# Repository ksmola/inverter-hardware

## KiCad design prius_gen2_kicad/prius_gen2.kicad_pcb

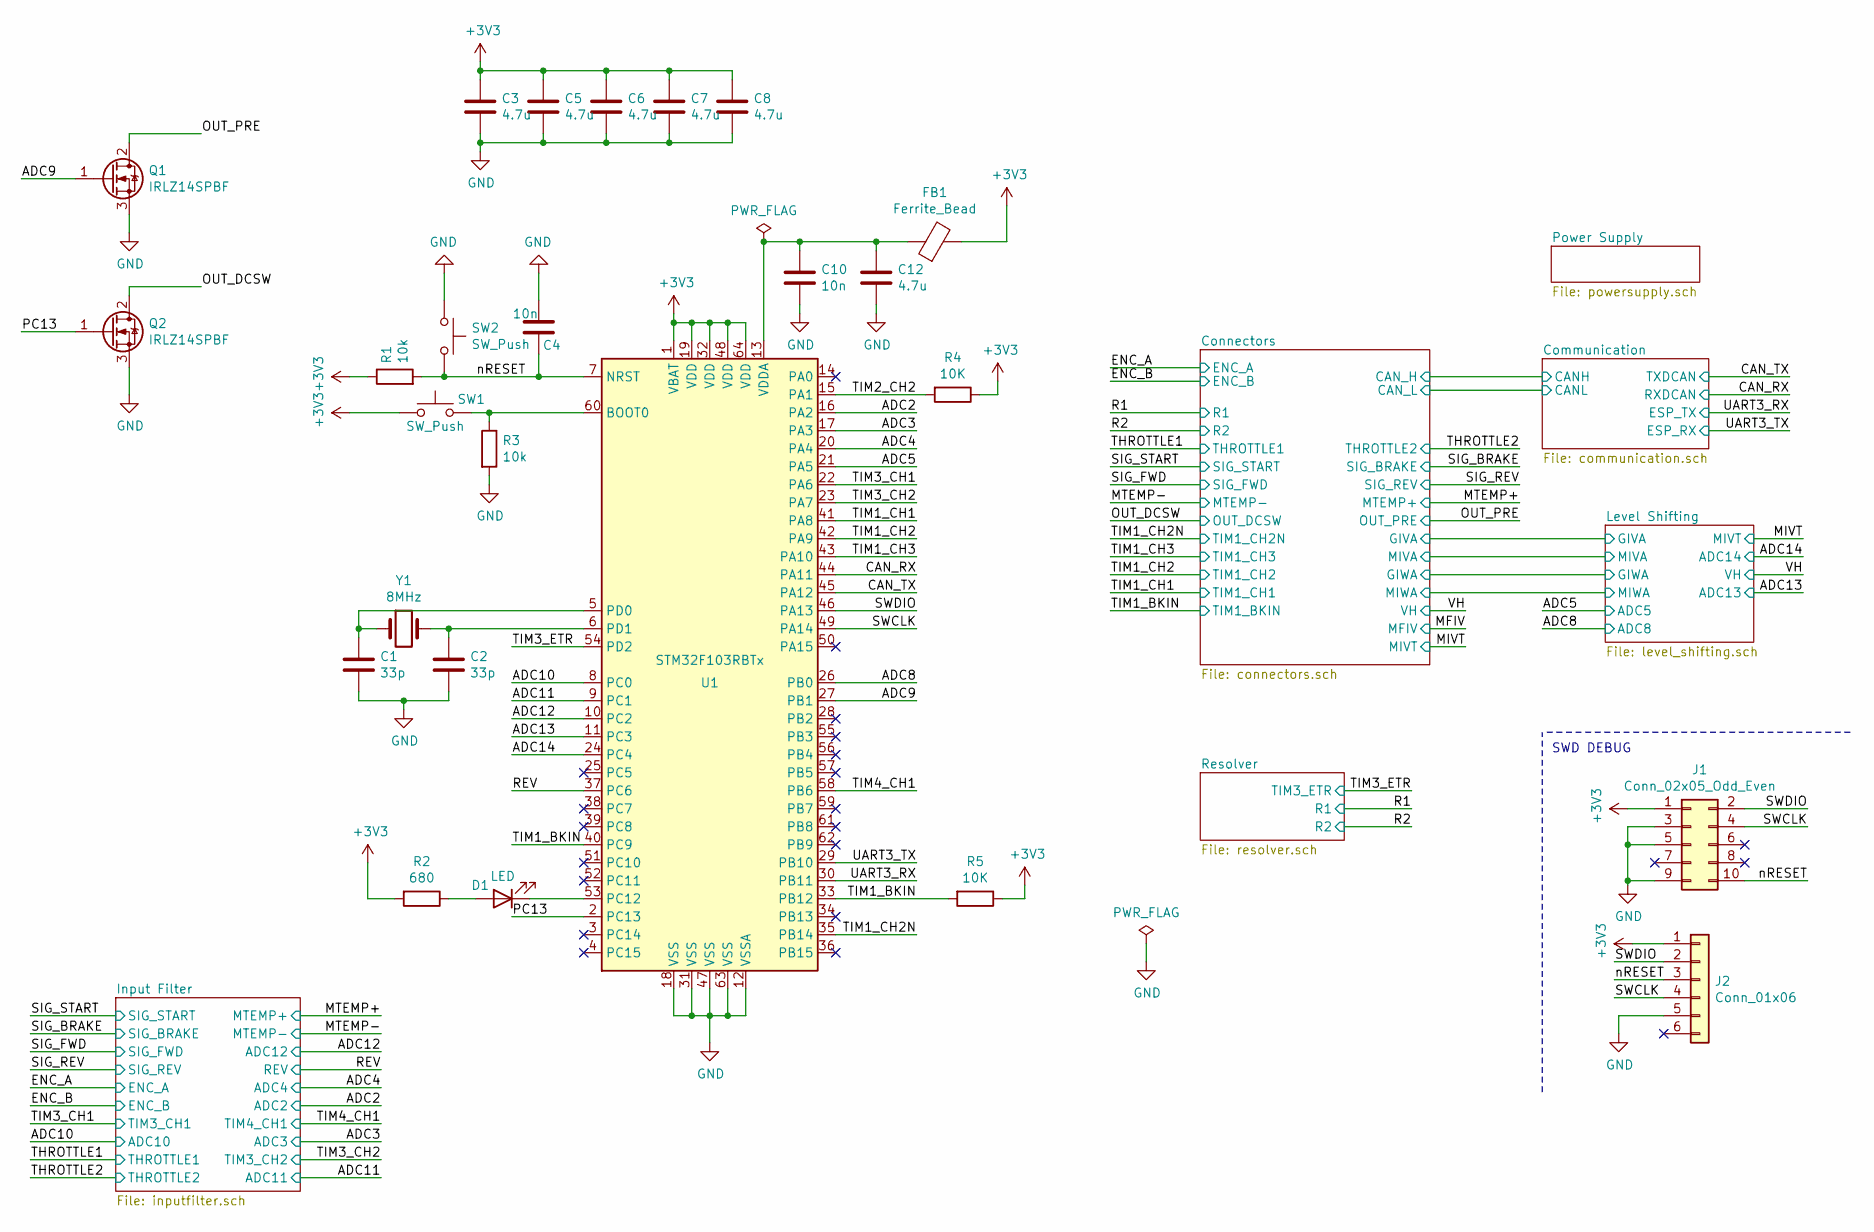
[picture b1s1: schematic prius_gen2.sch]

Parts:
C1, C2: 33p; C_0603_1608Metric
C3, C5, C6, C7, C8, C12: 4.7u; C_0603_1608Metric
C4, C10: 10n; C_0603_1608Metric
D1: LED; LED_0603_1608Metric_Castellated
FB1: Ferrite_Bead; C_0805_2012Metric
J1: Conn_02x05_Odd_Even; PinHeader_2x05_P1.27mm_Vertical_SMD
J2: Conn_01x06; Tag-Connect_TC2030-IDC-NL_2x03_P1.27mm_Vertical
Q1, Q2: IRLZ14SPBF; TO-252-2
R1, R3: 10k; R_0603_1608Metric
R2: 680; R_0603_1608Metric
R4, R5: 10K; R_0603_1608Metric
SW1, SW2: SW_Push; SW_SPST_EVQQ2
U1: STM32F103RBTx; LQFP-64_10x10mm_P0.5mm
Y1: 8MHz; Crystal_SMD_5032-2Pin_5.0x3.2mm

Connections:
/ADC2: U1.16 (PA2); also elsewhere on the board
/ADC3: U1.17 (PA3); also elsewhere on the board
/ADC4: U1.20 (PA4); also elsewhere on the board
/ADC5: U1.21 (PA5); also elsewhere on the board
/ADC8: U1.26 (PB0); also elsewhere on the board
/ADC9: Q1.1 (G), U1.27 (PB1)
/ADC10: U1.8 (PC0); also elsewhere on the board
/ADC11: U1.9 (PC1); also elsewhere on the board
/ADC12: U1.10 (PC2); also elsewhere on the board
/ADC13: U1.11 (PC3); also elsewhere on the board
/ADC14: U1.24 (PC4); also elsewhere on the board
/CAN_RX: U1.44 (PA11); also elsewhere on the board
/CAN_TX: U1.45 (PA12); also elsewhere on the board
/OUT_DCSW: Q2.2 (D); also elsewhere on the board
/OUT_PRE: Q1.2 (D); also elsewhere on the board
/PC13: Q2.1 (G), U1.2 (PC13)
/REV: U1.37 (PC6); also elsewhere on the board
/SWCLK: J1.4, J2.4, U1.49 (PA14)
/SWDIO: J1.2, J2.2, U1.46 (PA13)
/TIM1_BKIN: R5.2, U1.33 (PB12), U1.40 (PC9); also elsewhere on the board
/TIM1_CH1: U1.41 (PA8); also elsewhere on the board
/TIM1_CH2: U1.42 (PA9); also elsewhere on the board
/TIM1_CH2N: U1.35 (PB14); also elsewhere on the board
/TIM1_CH3: U1.43 (PA10); also elsewhere on the board
/TIM2_CH2: R4.2, U1.15 (PA1)
/TIM3_CH1: U1.22 (PA6); also elsewhere on the board
/TIM3_CH2: U1.23 (PA7); also elsewhere on the board
/TIM3_ETR: U1.54 (PD2); also elsewhere on the board
/TIM4_CH1: U1.58 (PB6); also elsewhere on the board
/UART3_RX: U1.30 (PB11); also elsewhere on the board
/UART3_TX: U1.29 (PB10); also elsewhere on the board
/nRESET: C4.1, J1.10, J2.3, R1.2, SW2.2, U1.7 (NRST)
GND: C1.1, C2.1, C3.2, C4.2, C5.2, C6.2, C7.2, C8.2, C10.2, C12.2, J1.3, J1.5, J1.9, J2.5, Q1.3 (S), Q2.3 (S), R3.2, SW2.1, U1.12 (VSSA), U1.18 (VSS), U1.31 (VSS), U1.47 (VSS), U1.63 (VSS); also elsewhere on the board
unnamed: C1.2, U1.5 (PD0), Y1.1
unnamed: C2.2, U1.6 (PD1), Y1.2
unnamed: C10.1, C12.1, FB1.1, U1.13 (VDDA)
unnamed: D1.1 (K), U1.53 (PC12)
unnamed: D1.2 (A), R2.1
unnamed: R3.1, SW1.2, U1.60 (BOOT0)

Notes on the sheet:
SWD DEBUG

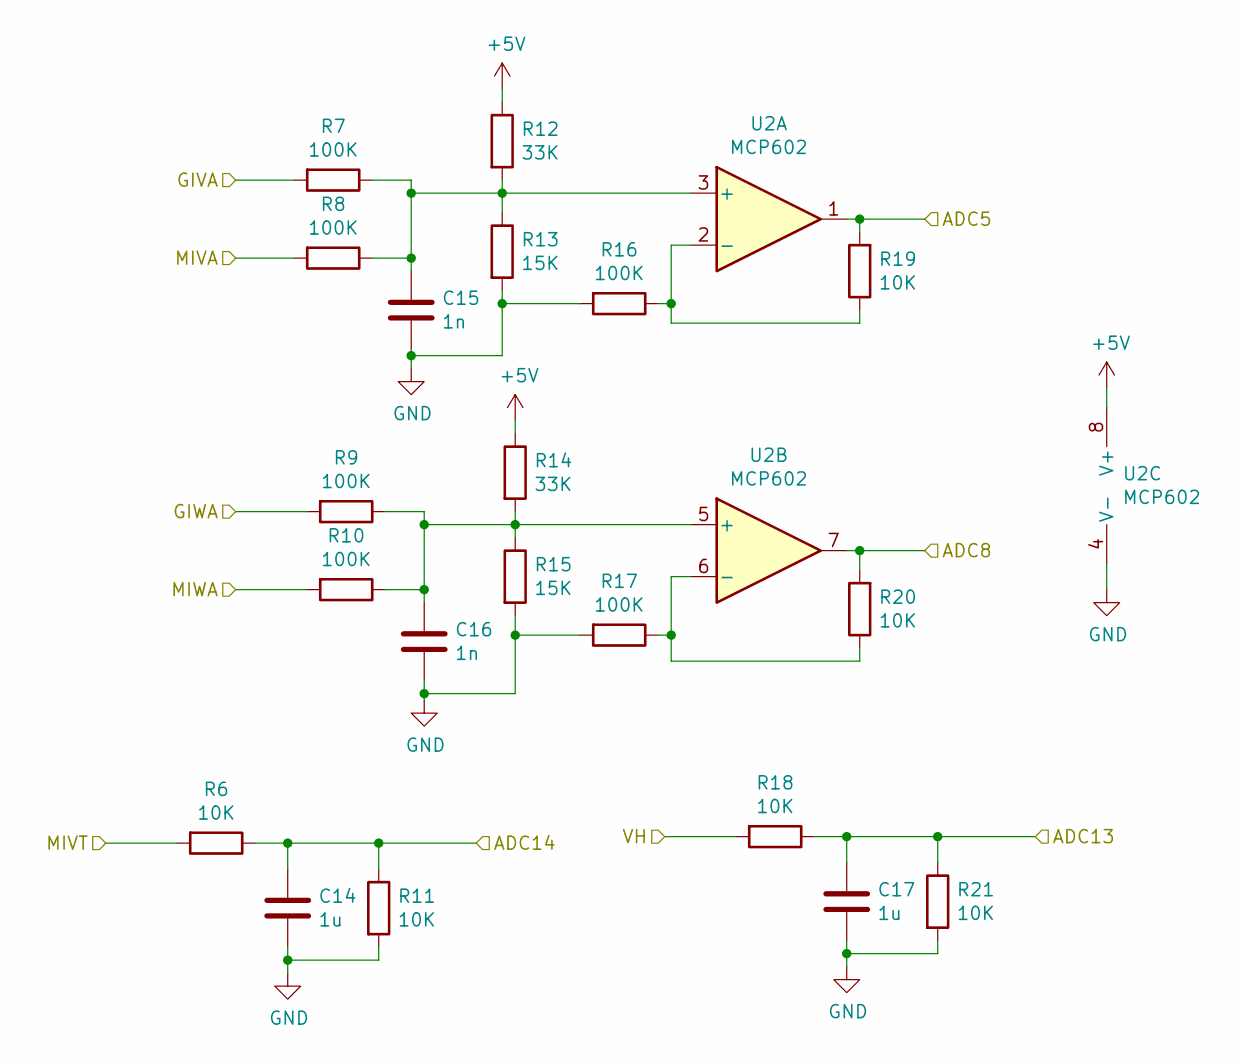
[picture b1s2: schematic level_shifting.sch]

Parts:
C14, C17: 1u; C_0603_1608Metric
C15, C16: 1n; C_0603_1608Metric
R6, R11, R18, R19, R20, R21: 10K; R_0603_1608Metric
R7, R8, R9, R10, R16, R17: 100K; R_0603_1608Metric
R12, R14: 33K; R_0603_1608Metric
R13, R15: 15K; R_0603_1608Metric
U2: MCP602; SOIC-8-1EP_3.9x4.9mm_P1.27mm_EP2.29x3mm

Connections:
+5V: R12.1, R14.1, U2.8 (V+); also elsewhere on the board
/ADC5: R19.2, U2.1; also elsewhere on the board
/ADC8: R20.2, U2.7; also elsewhere on the board
/ADC13: C17.1, R18.1, R21.1; also elsewhere on the board
/ADC14: C14.1, R6.1, R11.1; also elsewhere on the board
/Connectors/GIVA: R7.2; also elsewhere on the board
/Connectors/GIWA: R9.2; also elsewhere on the board
/Connectors/MIVA: R8.2; also elsewhere on the board
/Connectors/MIWA: R10.2; also elsewhere on the board
/MIVT: R6.2; also elsewhere on the board
/VH: R18.2; also elsewhere on the board
GND: C14.2, C15.2, C16.2, C17.2, R11.2, R13.2, R15.2, R16.2, R17.2, R21.2, U2.4 (V-); also elsewhere on the board
unnamed: C15.1, R7.1, R8.1, R12.2, R13.1, U2.3 (+)
unnamed: C16.1, R9.1, R10.1, R14.2, R15.1, U2.5 (+)
unnamed: R16.1, R19.1, U2.2 (-)
unnamed: R17.1, R20.1, U2.6 (-)

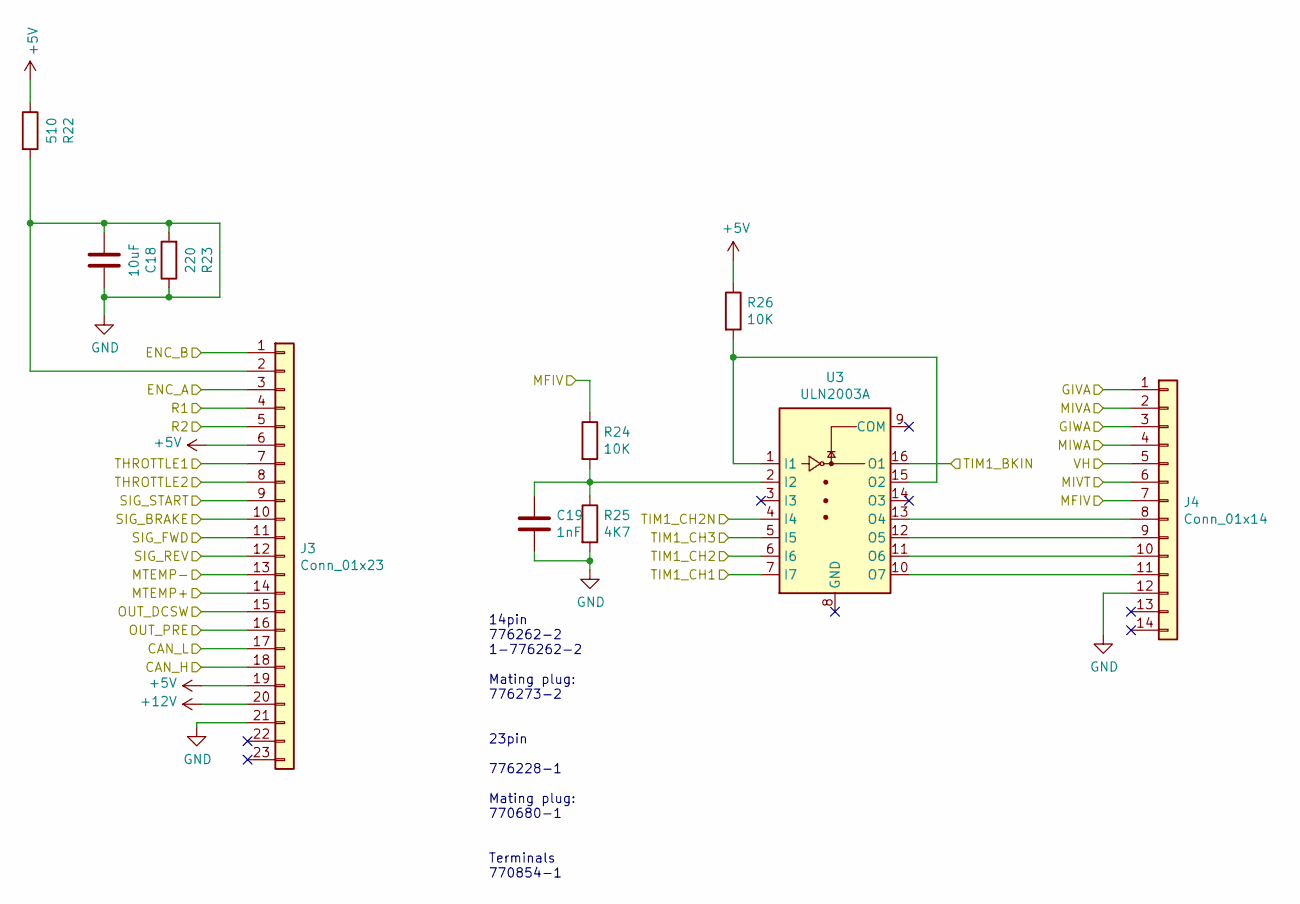
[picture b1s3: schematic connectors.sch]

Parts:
C18: 10uF; C_0603_1608Metric
C19: 1nF; C_0603_1608Metric
J3: Conn_01x23; TE_776228-1
J4: Conn_01x14; TE_776262-2
R22: 510; R_0603_1608Metric
R23: 220; R_0603_1608Metric
R24, R26: 10K; R_0603_1608Metric
R25: 4K7; R_0603_1608Metric
U3: ULN2003A; SOIC-16_4.55x10.3mm_P1.27mm

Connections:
+5V: J3.6, J3.19, R22.1, R26.1; also elsewhere on the board
+12V: J3.20; also elsewhere on the board
/Communication/CANH: J3.18; also elsewhere on the board
/Communication/CANL: J3.17; also elsewhere on the board
/Connectors/GIVA: J4.1; also elsewhere on the board
/Connectors/GIWA: J4.3; also elsewhere on the board
/Connectors/MIVA: J4.2; also elsewhere on the board
/Connectors/MIWA: J4.4; also elsewhere on the board
/ENC_A: J3.3; also elsewhere on the board
/ENC_B: J3.1; also elsewhere on the board
/MFIV: J4.7, R24.1
/MIVT: J4.6; also elsewhere on the board
/MTEMP+: J3.14; also elsewhere on the board
/MTEMP-: J3.13; also elsewhere on the board
/OUT_DCSW: J3.15; also elsewhere on the board
/OUT_PRE: J3.16; also elsewhere on the board
/R1: J3.4; also elsewhere on the board
/R2: J3.5; also elsewhere on the board
/SIG_BRAKE: J3.10; also elsewhere on the board
/SIG_FWD: J3.11; also elsewhere on the board
/SIG_REV: J3.12; also elsewhere on the board
/SIG_START: J3.9; also elsewhere on the board
/THROTTLE1: J3.7; also elsewhere on the board
/THROTTLE2: J3.8; also elsewhere on the board
/TIM1_BKIN: U3.16 (O1); also elsewhere on the board
/TIM1_CH1: U3.7 (I7); also elsewhere on the board
/TIM1_CH2: U3.6 (I6); also elsewhere on the board
/TIM1_CH2N: U3.4 (I4); also elsewhere on the board
/TIM1_CH3: U3.5 (I5); also elsewhere on the board
/VH: J4.5; also elsewhere on the board
GND: C18.1, C18.2, C19.2, J3.2, J3.21, J4.12, R22.2, R23.1, R23.2, R25.2; also elsewhere on the board
unnamed: C19.1, R24.2, R25.1, U3.2 (I2)
unnamed: J4.8, U3.13 (O4)
unnamed: J4.9, U3.12 (O5)
unnamed: J4.10, U3.11 (O6)
unnamed: J4.11, U3.10 (O7)
unnamed: R26.2, U3.1 (I1), U3.15 (O2)

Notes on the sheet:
14pin 776262-2 1-776262-2 Mating plug: 776273-2 23pin 776228-1 Mating plug: 770680-1 Terminals 770854-1

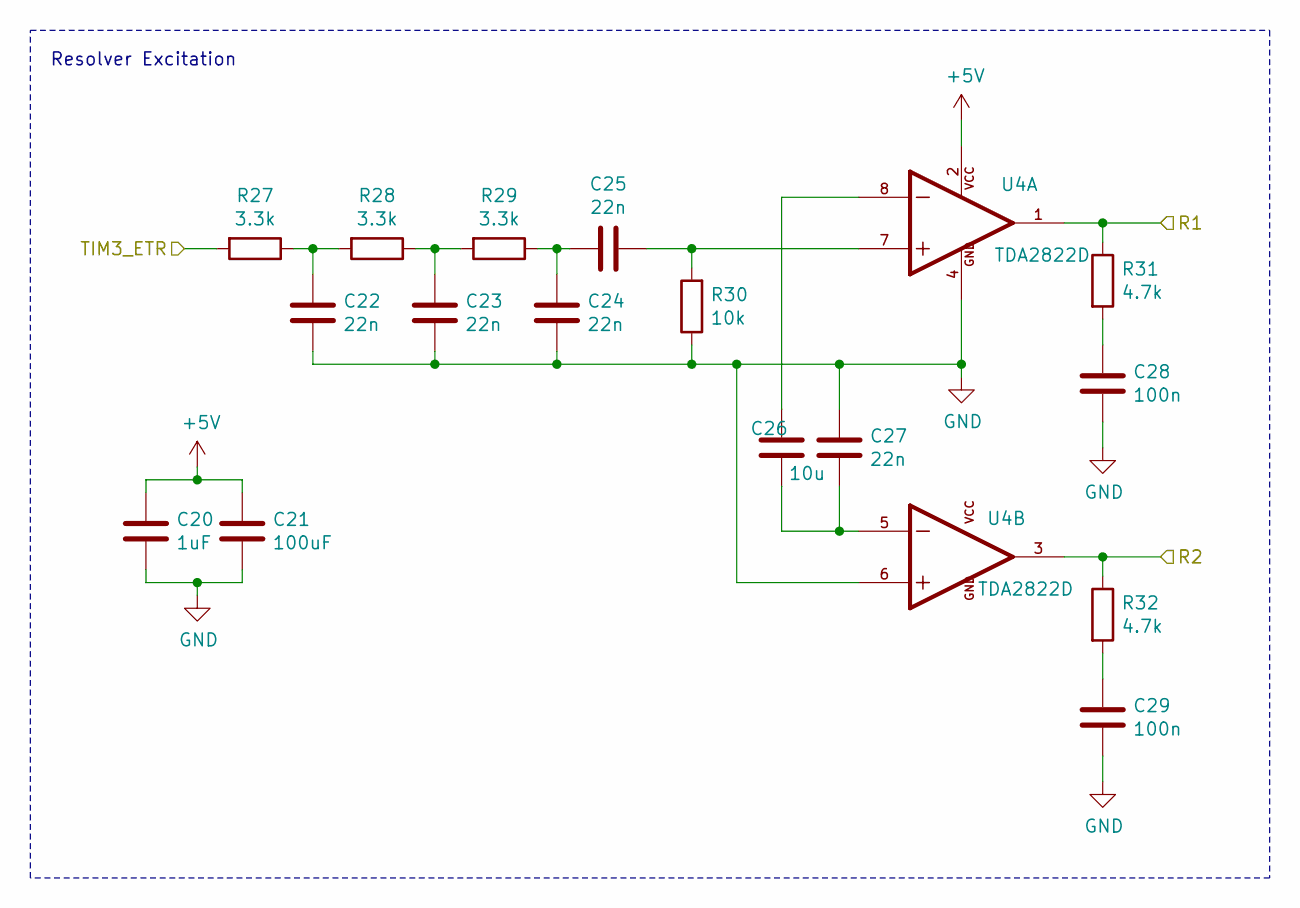
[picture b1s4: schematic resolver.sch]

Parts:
C20: 1uF; C_0603_1608Metric
C21: 100uF; C_Elec_6.3x7.7
C22, C23, C24, C25, C27: 22n; C_0603_1608Metric
C26: 10u; C_0603_1608Metric
C28, C29: 100n; C_0603_1608Metric
R27, R28, R29: 3.3k; R_0603_1608Metric
R30: 10k; R_0603_1608Metric
R31, R32: 4.7k; R_0603_1608Metric
U4: TDA2822D; SOIC-8-1EP_3.9x4.9mm_P1.27mm_EP2.29x3mm; PARTREV September 2003

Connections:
+5V: C20.1, C21.1, U4.2; also elsewhere on the board
/R1: R31.1, U4.1; also elsewhere on the board
/R2: R32.1, U4.3; also elsewhere on the board
/TIM3_ETR: R27.2; also elsewhere on the board
GND: C20.2, C21.2, C22.2, C23.2, C24.2, C27.1, C28.2, C29.2, R30.1, U4.4, U4.6; also elsewhere on the board
unnamed: C22.1, R27.1, R28.2
unnamed: C23.1, R28.1, R29.2
unnamed: C24.1, C25.2, R29.1
unnamed: C25.1, R30.2, U4.7
unnamed: C26.1, U4.8
unnamed: C26.2, C27.2, U4.5
unnamed: C28.1, R31.2
unnamed: C29.1, R32.2

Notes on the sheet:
Resolver Excitation

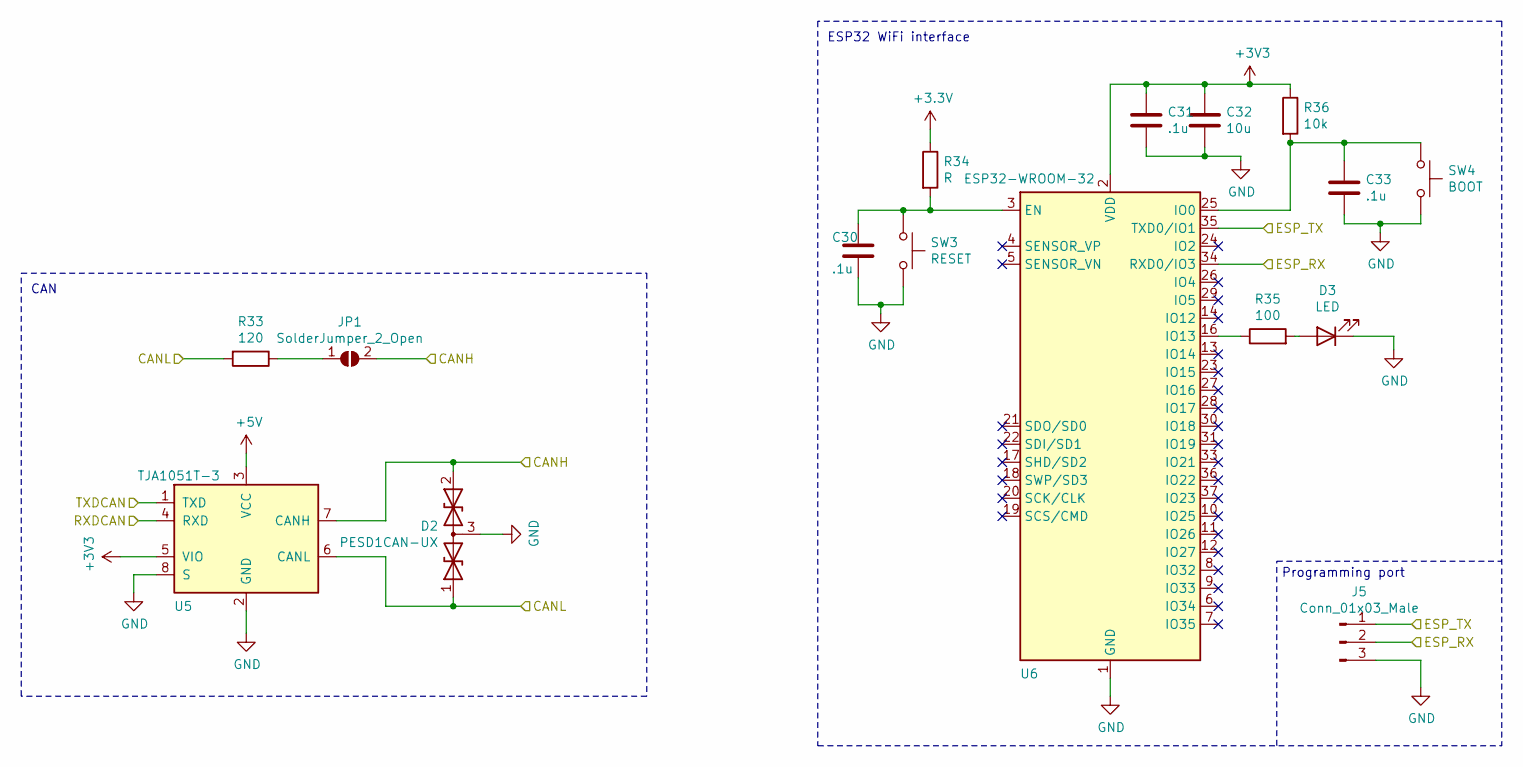
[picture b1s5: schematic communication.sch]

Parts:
C30, C31, C33: .1u; C_0603_1608Metric
C32: 10u; C_0603_1608Metric
D2: PESD1CAN-UX; SOT-323_SC-70
D3: LED; LED_0603_1608Metric_Castellated
J5: Conn_01x03_Male; PinSocket_1x03_P1.27mm_Vertical_SMD_Pin1Left
JP1: SolderJumper_2_Open; SolderJumper-2_P1.3mm_Open_TrianglePad1.0x1.5mm
R33: 120; R_0603_1608Metric
R34: R; R_0603_1608Metric
R35: 100; R_0603_1608Metric
R36: 10k; R_0603_1608Metric
SW3: RESET; SW_SPST_EVQQ2
SW4: BOOT; SW_SPST_EVQQ2
U5: TJA1051T-3; SOIC-8_3.9x4.9mm_P1.27mm
U6: ESP32-WROOM-32

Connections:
+5V: U5.3 (VCC); also elsewhere on the board
/CAN_RX: U5.4 (RXD); also elsewhere on the board
/CAN_TX: U5.1 (TXD); also elsewhere on the board
/Communication/CANH: D2.2 (A2), JP1.2 (B), U5.7 (CANH); also elsewhere on the board
/Communication/CANL: D2.1 (A1), R33.2, U5.6 (CANL); also elsewhere on the board
/UART3_RX: J5.1, U6.35 (TXD0/IO1); also elsewhere on the board
/UART3_TX: J5.2, U6.34 (RXD0/IO3); also elsewhere on the board
GND: C30.2, C31.2, C32.2, C33.2, D2.3 (common), D3.1 (K), J5.3, SW3.2, SW4.2, U5.2 (GND), U5.8 (S), U6.1 (GND), U6.15 (GND), U6.38 (GND), U6.39 (GND); also elsewhere on the board
unnamed: C30.1, R34.2, SW3.1, U6.3 (EN)
unnamed: C33.1, R36.2, SW4.1, U6.25 (IO0)
unnamed: D3.2 (A), R35.2
unnamed: JP1.1 (A), R33.1
unnamed: R35.1, U6.16 (IO13)

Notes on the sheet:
Programming port
CAN
ESP32 WiFi interface

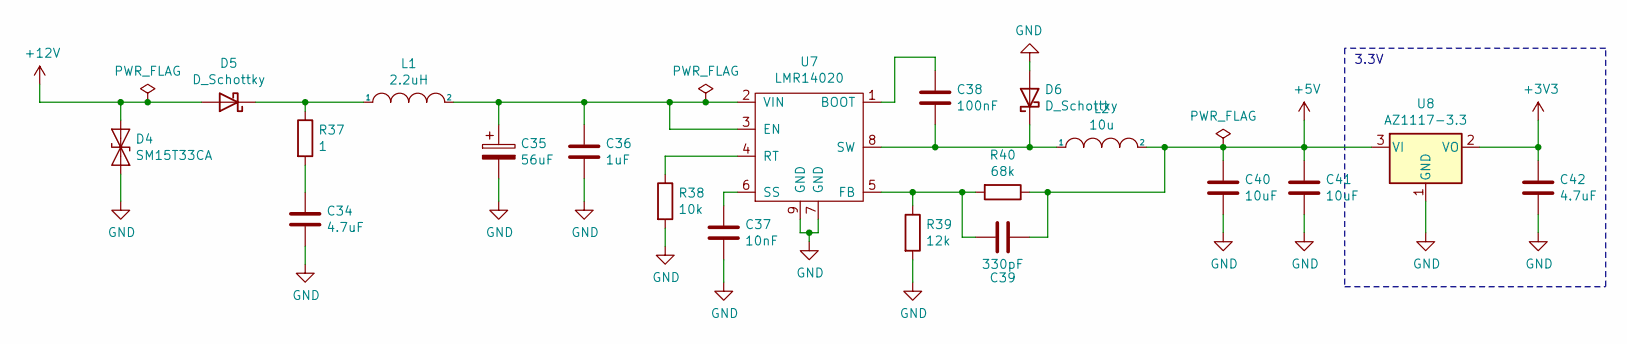
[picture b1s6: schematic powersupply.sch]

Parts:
C34, C42: 4.7uF; C_0603_1608Metric
C35: 56uF; CP_Radial_D8.0mm_P3.50mm
C36: 1uF; C_0603_1608Metric
C37: 10nF; C_0603_1608Metric
C38: 100nF; C_0603_1608Metric
C39: 330pF; C_0603_1608Metric
C40, C41: 10uF; C_0603_1608Metric
D4: SM15T33CA; D_SMC
D5, D6: D_Schottky; D_SMA
L1: 2.2uH; L_1210_3225Metric
L2: 10u; MWSA0503
R37: 1; R_0603_1608Metric
R38: 10k; R_0603_1608Metric
R39: 12k; R_0603_1608Metric
R40: 68k; R_0603_1608Metric
U7: LMR14020; SOIC-8-1EP_3.9x4.9mm_P1.27mm_EP2.29x3mm
U8: AZ1117-3.3; SOT-223-3_TabPin2

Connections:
+5V: C39.2, C40.1, C41.1, L2.2, R40.1, U8.3 (VI); also elsewhere on the board
+12V: D4.1 (A1), D5.2 (A); also elsewhere on the board
GND: C34.2, C35.2, C36.2, C37.2, C40.2, C41.2, C42.2, D4.2 (A2), D6.2 (A), R38.2, R39.2, U7.7 (GND), U7.9 (GND), U8.1 (GND); also elsewhere on the board
unnamed: C34.1, R37.2
unnamed: C35.1, C36.1, L1.2, U7.2 (VIN), U7.3 (EN)
unnamed: C37.1, U7.6 (SS)
unnamed: C38.1, U7.1 (BOOT)
unnamed: C38.2, D6.1 (K), L2.1, U7.8 (SW)
unnamed: C39.1, R39.1, R40.2, U7.5 (FB)
unnamed: D5.1 (K), L1.1, R37.1
unnamed: R38.1, U7.4 (RT)

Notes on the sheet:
3.3V

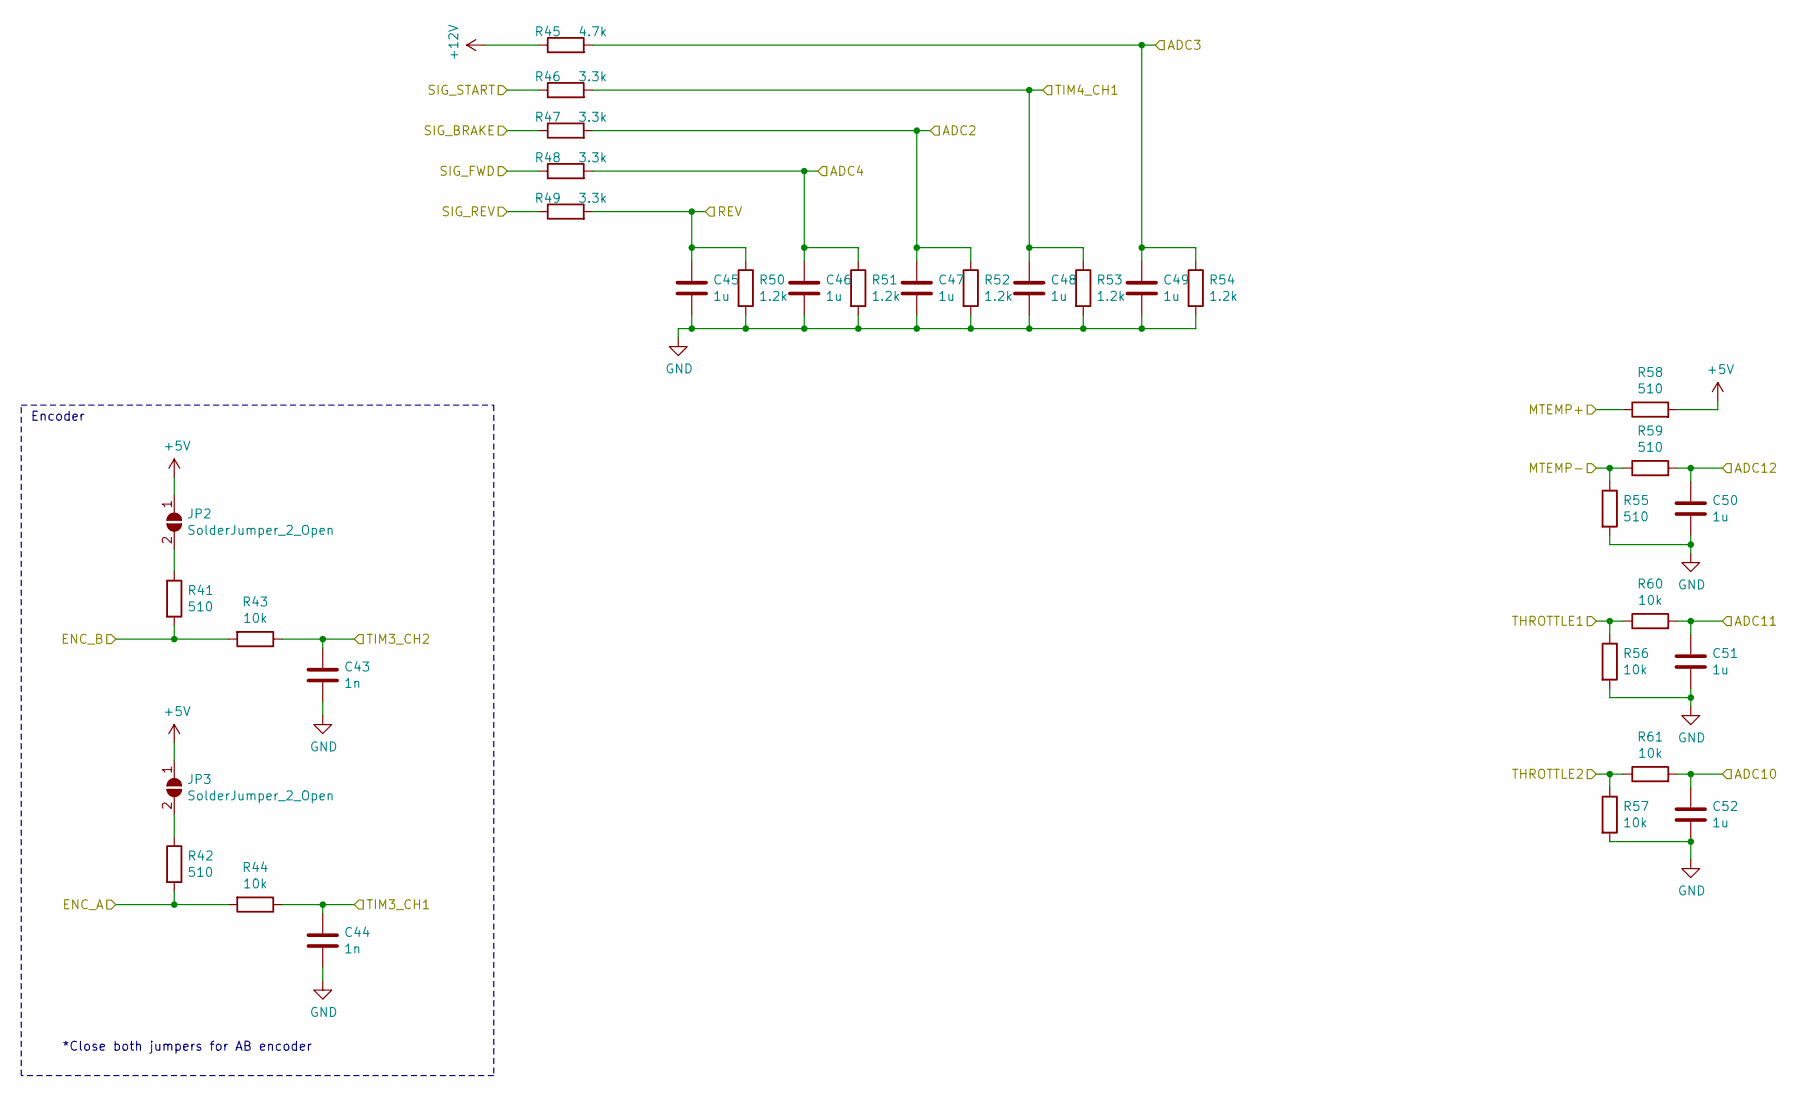
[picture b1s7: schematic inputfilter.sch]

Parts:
C43, C44: 1n; C_0603_1608Metric
C45, C46, C47, C48, C49, C50, C51, C52: 1u; C_0603_1608Metric
JP2, JP3: SolderJumper_2_Open; SolderJumper-2_P1.3mm_Open_TrianglePad1.0x1.5mm
R41, R42, R55, R58, R59: 510; R_0603_1608Metric
R43, R44, R56, R57, R60, R61: 10k; R_0603_1608Metric
R45: 4.7k; R_0603_1608Metric
R46, R47, R48, R49: 3.3k; R_0603_1608Metric
R50, R51, R52, R53, R54: 1.2k; R_0603_1608Metric

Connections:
+5V: JP2.1 (A), JP3.1 (A), R58.2; also elsewhere on the board
+12V: R45.1; also elsewhere on the board
/ADC2: C47.1, R47.2, R52.1; also elsewhere on the board
/ADC3: C49.1, R45.2, R54.1; also elsewhere on the board
/ADC4: C46.1, R48.2, R51.1; also elsewhere on the board
/ADC10: C52.1, R61.2; also elsewhere on the board
/ADC11: C51.1, R60.2; also elsewhere on the board
/ADC12: C50.1, R59.2; also elsewhere on the board
/ENC_A: R42.2, R44.2; also elsewhere on the board
/ENC_B: R41.2, R43.2; also elsewhere on the board
/MTEMP+: R58.1; also elsewhere on the board
/MTEMP-: R55.1, R59.1; also elsewhere on the board
/REV: C45.1, R49.2, R50.1; also elsewhere on the board
/SIG_BRAKE: R47.1; also elsewhere on the board
/SIG_FWD: R48.1; also elsewhere on the board
/SIG_REV: R49.1; also elsewhere on the board
/SIG_START: R46.1; also elsewhere on the board
/THROTTLE1: R56.1, R60.1; also elsewhere on the board
/THROTTLE2: R57.1, R61.1; also elsewhere on the board
/TIM3_CH1: C44.1, R44.1; also elsewhere on the board
/TIM3_CH2: C43.1, R43.1; also elsewhere on the board
/TIM4_CH1: C48.1, R46.2, R53.1; also elsewhere on the board
GND: C43.2, C44.2, C45.2, C46.2, C47.2, C48.2, C49.2, C50.2, C51.2, C52.2, R50.2, R51.2, R52.2, R53.2, R54.2, R55.2, R56.2, R57.2; also elsewhere on the board
unnamed: JP2.2 (B), R41.1
unnamed: JP3.2 (B), R42.1

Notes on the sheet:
Encoder
*Close both jumpers for AB encoder

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
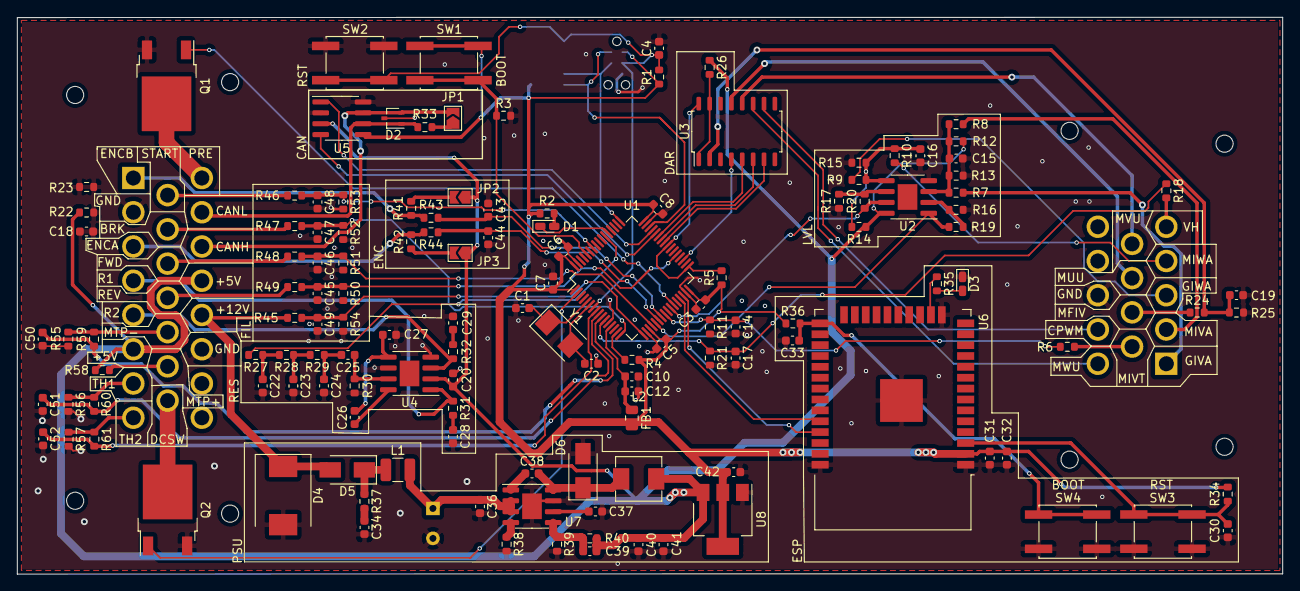
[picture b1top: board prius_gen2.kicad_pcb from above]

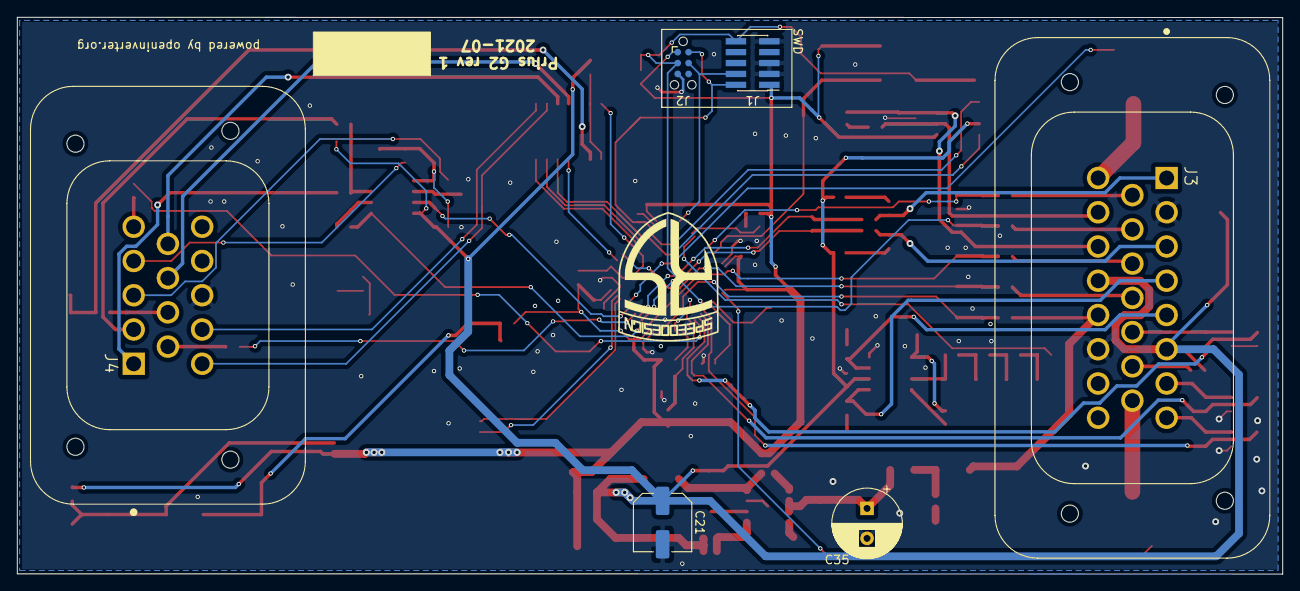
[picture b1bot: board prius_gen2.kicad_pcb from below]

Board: 2 copper layers, 147.8 x 65.0 mm, 141 parts (6 on the bottom side), 96 nets.

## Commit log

2021-06-24 prius gen2 kicad, first steps
2021-07-02 more schematics
2021-07-04 schematics almost done
2021-07-04 fixed ERC
2021-07-05 started routing
2021-07-11 cam and more...
